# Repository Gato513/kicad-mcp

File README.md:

# kicad-mcp

An MCP (Model Context Protocol) server that lets an LLM agent operate
[KiCad](https://www.kicad.org/) directly — read schematics and PCBs in a
token-efficient format, place footprints, draw copper, run an autorouter,
validate with ERC/DRC, and export manufacturing files — through 32
purpose-built tools instead of raw file editing.

**Status:** past MVP. The full PCB write loop (placement → outline →
zones/GND plane → autorouting → DRC → export) has been closed and
re-validated against real KiCad 10.0.4 for months. It is now in a
pre-release consolidation phase: a structured [Validation
Suite](validation-suite/) exercises the flow against real open-hardware
projects to find where it actually breaks, on purpose, before anyone else
does. See [Known limitations](#known-limitations) below — this README
leads with them rather than burying them.

## What it does

kicad-mcp automates the canonical KiCad PCB flow: place footprints → draw
board outline → add copper zones/GND plane → route with
[Freerouting](https://github.com/freerouting/freerouting) (headless
autorouter) → refill zones and re-run DRC → export gerbers/BOM/renders.
State is exposed to the LLM agent as [TOON](docs/specs/toon-v1.md), a
compact encoding designed to keep token usage low across many small tool
calls rather than re-serializing the whole board every time.

It talks to a **running KiCad instance** over KiCad's own local IPC API
(`kicad-python`) for live edits, and shells out to `kicad-cli` for
DRC/ERC/export — it does not parse or hand-edit `.kicad_pcb`/`.kicad_sch`
files itself for PCB work (schematic editing is the one exception, see
limitation 7 below).

**Validated scale, stated plainly:** the flow has completed end-to-end,
with results within the project's own acceptance thresholds, on boards up
to **63 footprints / 48 nets / 2 layers**. It was also run against a
**437-footprint / 380-net / 4-layer** board (HackRF One) specifically to
find the scaling ceiling — the autorouter did not complete on that board
(see limitation 2). Treat "small-to-medium 2-layer board" as the
demonstrated sweet spot today, not "any KiCad project."

## Quickstart

```bash
git clone https://github.com/Gato513/kicad-mcp.git
cd kicad-mcp
uv sync                                   # install dependencies (uv, https://docs.astral.sh/uv/)
python3 scripts/verificar_entorno.py      # environment check — run this before anything else
uv run pytest -m "not integration"        # offline unit + golden tests (394 passing today)
```

`verificar_entorno.py` tells you exactly what's missing for the mode
you're in (plain unit tests vs. tests that need a running KiCad) and
prints the fix, so start there rather than guessing at env vars.

To actually drive KiCad you need:
- KiCad ≥ 9.0 installed, 10.0.4 is the validated target (see
  [ADR-0002](docs/adr/0002-versiones-de-kicad.md)), with **Preferences →
  Plugins → Enable API server** turned on and KiCad restarted.
- `KICAD_MCP_PROJECT` set to the `.kicad_pro` you want the server to
  operate on.
- `KICAD_MCP_FREEROUTING_JAR` set to a local `freerouting-*.jar` if you
  want `route_board` to actually autoroute (Java ≥ 17 required — note
  Freerouting ≥ 2.2.3 itself needs Java 25; if your PATH `java` is
  older, point `KICAD_MCP_JAVA_EXE` at a compatible JDK instead of
  changing your system default).
- `KICAD_API_SOCKET` only if your KiCad API socket isn't at the default
  `ipc:///tmp/kicad/api.sock`.

Then register the server with an MCP client (`uv run kicad-mcp` runs it
over stdio) or probe it by hand with the official inspector:

```bash
npx @modelcontextprotocol/inspector uv run kicad-mcp
```

A minimal first call once connected: `health()` to confirm the bridge can
see your KiCad instance, then `run_drc()` against a project you don't
mind DRC-checking.

## Known limitations

This section exists because a colleague who tries this on their own board
deserves to know where it stops working *before* they hit it, not after.
Each item links to the session or document where it was found and
verified — nothing here is a guess.

- **Validated up to 63 footprints / 2 layers; a 437-footprint / 4-layer
  board found the scaling ceiling, not a routed result.** See
  [`docs/analisis/validation-suite-sintesis-A-B-C.md`](docs/analisis/validation-suite-sintesis-A-B-C.md)
  for the full three-point comparison (13 fp → 63 fp → 437 fp).
- **Freerouting 2.1.0 can enter an internal crash-loop on large/complex
  boards** (observed on the 437-footprint board: repeated internal
  `NullPointerException`s, no routing progress for a full hour). This is
  an upstream Freerouting issue, not a kicad-mcp bug — `route_board`
  itself behaved correctly on the timeout (no corrupted state). See
  [`docs/BACKLOG.md`](docs/BACKLOG.md) (`F-V3-ROUTER-TIMEOUT-HARD`).
- **`add_zone(fill=true)` can crash KiCad after 3-4 consecutive calls on
  large boards.** Root cause is not conclusively identified — code
  analysis found no bridge-side cause, and the failure signature (zone
  fragmentation) looks like a pcbnew fill behavior at scale, but this
  wasn't confirmed by reproduction this cycle. Workaround: call
  `fill_zones()` once at the end instead of `fill=true` per zone. Full
  writeup: [`docs/analisis/auditoria-contratos-bridge.md`](docs/analisis/auditoria-contratos-bridge.md) §4.
- **Most write tools don't save to disk by themselves.** Tools like
  `add_track`, `add_via`, `move_footprint` mutate the live, in-memory
  board and expect the caller to invoke `save_board()` explicitly. The
  tools that guarantee disk == memory when they return successfully are
  `route_board`, `fill_zones`, `add_zone(fill=true)`, and
  `delete_tracks_bulk` when the board has copper zones — see
  [ADR-0012](docs/adr/0012-route-board-persist-contract.md).
- **`delete_tracks_bulk` behaves differently depending on the board.** If
  the board contains at least one copper zone — a board-wide check, not a
  geometric test of whether the deletion actually touched that zone — it
  refills zones, re-enforces hole clearance and saves to disk before
  returning, raising `POST_ZONE_PERSIST_FAILED` if that save fails rather
  than succeeding silently. On a board with no copper zone it stays
  in-memory like the tools above, and `save_board()` is the caller's job.
  `delete_zone` and `add_keepout_zone` don't recompute neighboring zone
  fills on their own — tracked as `A2`/`A3` in
  [`docs/analisis/auditoria-contratos-bridge.md`](docs/analisis/auditoria-contratos-bridge.md) §5.2.
- **Freerouting doesn't treat a GND copper plane as an exclusion zone for
  nets it doesn't own** — it only routes to the plane's own net, not
  around it. A specific same-layer variant of the resulting orphaned-via
  pattern isn't fixed by the existing post-route stitching yet. See
  `F-D5-01-B` in [`docs/BACKLOG.md`](docs/BACKLOG.md).
- **Schematic editing is direct file mutation (`kicad-skip`), not IPC** —
  KiCad 10 doesn't expose a schematic API. This also means the schematic
  write tools (`add_symbol`, `set_value`, `set_footprint`,
  `connect_pins`) are purely additive today: there's no `delete_wire` or
  similar, so an agent can build a schematic but not clean one up. See
  [`docs/guias/guia-paleta.md`](docs/guias/guia-paleta.md) for the one
  real hazard this creates (never edit a schematic file while KiCad's
  own editor has it open).
- **Long-running tool calls (e.g. a full autoroute) can exceed an MCP
  client's idle timeout** (~1818s observed) before KiCad/Freerouting
  finishes. This is a client-side limitation, not a kicad-mcp bug —
  driving the call from a detached process (`nohup` + `disown`) works
  around it. See `docs/historico/sesiones/33-reporte.md`.
- **GUI-dependent tests require a human with KiCad open and are not
  automated** — this is a constraint of KiCad's IPC API on this version,
  not a project shortcut. See
  [`docs/guias/pruebas-gui.md`](docs/guias/pruebas-gui.md) for the manual
  protocol.
- **Practically Linux-only** ([ADR-0005](docs/adr/0005-linux-como-plataforma.md)).
  KiCad 10.0.4 is the validated target; 9.0 is the documented minimum
  ([ADR-0002](docs/adr/0002-versiones-de-kicad.md)).

## Documentation

- [`docs/analisis/validation-suite-sintesis-A-B-C.md`](docs/analisis/validation-suite-sintesis-A-B-C.md) — the
  cross-board evidence behind the scale claims above.
- [`docs/analisis/auditoria-contratos-bridge.md`](docs/analisis/auditoria-contratos-bridge.md) — full audit of
  every write tool's persistence/error/sync/reload contract.
- [`docs/adr/`](docs/adr/) — one architectural decision record per file
  (why KiCad 10, why stdio-only, why no database, the `route_board`
  persistence contract, etc.).
- [`docs/architecture-for-contributors.md`](docs/architecture-for-contributors.md)
  — start here if you're new: real process topology, tool taxonomy, and
  how to navigate the ADRs/specs/session-report layers below.
- [`docs/DECISIONES.md`](docs/DECISIONES.md) — index of ADRs plus
  informal decisions not yet promoted to one.
- [`docs/investigacion/`](docs/investigacion/) — root-cause
  investigation reports for specific bugs.
- [`docs/glosario.md`](docs/glosario.md) — EDA/KiCad domain glossary.
- [`docs/guias/guia-paleta.md`](docs/guias/guia-paleta.md) — protocol for
  populating a schematic with `add_symbol`.
- [`docs/guias/pruebas-gui.md`](docs/guias/pruebas-gui.md) — manual test
  protocol for the GUI-dependent test suite.
- [`docs/INDEX.md`](docs/INDEX.md) — full documentation map, if you need
  something not linked above.

## Contributing

Contributions are welcome. [`CONTRIBUTING.md`](CONTRIBUTING.md) covers
setup, the project's write-tool contract (the 4 axes every write tool is
checked against), and the review conventions that shaped the codebase —
read it before opening a PR that touches anything under `src/kicad_mcp/tools/`
or `src/kicad_mcp/bridge/`.

## License

Apache License 2.0 — see [`LICENSE`](LICENSE). Runtime dependencies with
other licenses (KiCad and Freerouting are GPL-3.0, invoked as external
processes rather than linked; `kicad-skip` is LGPL-2.1) are listed in
[`NOTICE`](NOTICE).

## Acknowledgments

- [KiCad](https://www.kicad.org/) — the EDA platform this project
  automates, not replaces.
- [Freerouting](https://github.com/freerouting/freerouting) — the
  headless autorouter `route_board` drives. Its 2.1.0 crash-loop on large
  boards is a real, documented limitation (see above) — it's still the
  best open autorouter available for this integration.
- [ANAVI Technology](https://anavi.technology/) and [Great Scott
  Gadgets](https://greatscottgadgets.com/) — authors of the real
  open-hardware designs (`anavi-dev-mic`, `anavi-macro-pad-12`,
  `hackrf-one`) used as ground truth in the Validation Suite.
- Built with heavy use of Claude (Anthropic) as the agentic development
  environment throughout this project's write-tool implementation and
  validation cycles — noted here for transparency about how the codebase
  was produced, not as an endorsement of any particular workflow.

*(También disponible en [español](README.es.md).)*

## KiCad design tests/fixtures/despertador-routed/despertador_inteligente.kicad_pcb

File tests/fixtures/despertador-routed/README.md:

# Fixture `despertador-routed`

## Actualizado en sesión 29 (Dogfooding 7, 2026-07-25, commit base `6479923`)

Este fixture fue **regenerado desde cero** en la sesión 29 (Dogfooding 7,
tercer dogfooding de Fase 3), partiendo del mismo esquemático corregido de
sesión 19b usado en D3-D6 (0 errores ERC, 4 warnings `lib_symbol_mismatch`
aceptados — D-19b.1). Reemplaza al fixture de sesión 28 (D6): misma placa,
misma topología eléctrica, **colocación física nueva** (V6 de D7 — 23
coordenadas propias, distintas de D5/D6, decididas por el agente en clusters
funcionales dispuestos en anti-diagonal, no imitación de D5/D6).

**Objetivo de D7:** (a) 3er verde consecutivo del criterio de cierre de
Fase 3 (D5=9.5, D6=9.7, D7=9.8 — ver detalle abajo); (b) aislar
correctamente el efecto de D-26.1 (sesión 26) replicando el orden de fases
exacto de D5 (plano GND creado ANTES de la colocación, D-28.1 vinculante) —
a diferencia de D6, donde el orden invertido dejó el experimento
confundido; (c) variación geométrica controlada (V6) para que la evidencia
de D-23.2/D-26.1 no dependa de un único layout; (d) protocolo F-D6-01 (V7):
3 mediciones adicionales de re-ruteo parcial para cerrar la vigilancia
sobre el costo de `route_board` en re-ruteos parciales. Ver
`/tmp/dogfood7-fricciones.md` (log completo de la sesión, no versionado)
para el detalle de las 4 corridas completas de ruteo + experimento V4.

- Topología de red: idéntica a D3-D6 (`/NSS` separado de `/MOSI`, `/SCL`
  limpio, No-Connect explícitos en U2.INT/U3.~INT/U3.VLED+).

## Uso

Estos tests son `integration_gui`: necesitan KiCad vivo con **una copia**
de este fixture abierta (no hay `open_project` programático en kipy/KiCad
10). Ver `docs/pruebas-gui.md §fixture despertador-routed` para el
protocolo completo. **Ningún test de este repo hardcodea las coordenadas de
colocación** — todos derivan bbox/zonas/posiciones en runtime (D-24.1), así
que el cambio de layout D6→D7 no afecta ninguna aserción existente.

## Estado del ruteo

- Board: 44×44mm (contorno `(125,60)`→`(169,104)`, idéntico a D3-D6), plano
  GND en B.Cu filled desde cero **antes** de la colocación (orden D5/D-28.1,
  no D6) y antes del ruteo (C2, Freerouting no respeta el plano como
  exclusión de nets ajenos — D-19.1 v6 — se resuelve con refill +
  `enforce_hole_clearance` + persistencia D-23.2 post-route).
- **Colocación (V6, coordenadas nuevas):** clusters funcionales en
  anti-diagonal — BT1 (batería) en la banda superior, cluster de potencia
  (C1/D1/TP1/TP2) arriba-derecha, J1+U1 (MCU, hub SPI/I2C) en banda media,
  U4 (RF) + ANT1 pegada a 2mm de distancia (vs 28mm en D5/D6) en el
  cuadrante inferior-derecho, cluster I2C (U2/U3/C5/C6/R1/R2/J2) en el
  cuadrante izquierdo. `get_footprint_neighbors` inclusivo (D-D4.1) corrido
  sobre BT1, U4, J1, J2, ANT1 antes de mover — con el outline ya creado
  (orden D-28.1), a diferencia de D6. Verificación read-only adicional de
  solapes de courtyard tras la colocación: 0 solapes, los 23 dentro del
  outline, ANT1 a 15mm del borde y J1 a 7.5mm (ambos muy por encima del
  mínimo 1.5-2mm de D-D3.1).
- **Experimento aislado D-26.1 (V4.a → V4.b, el punto metodológico central
  de D7):** con el orden de fases correcto (plano antes de colocar, sin
  confundir con D6), el baseline **sin** `fill_zones()` explícito (V4.a)
  reprodujo el patrón exacto de D5: **6 violaciones no-triviales** (3×
  `hole_clearance` J1 NPTH + 1× `hole_clearance` ANT1 + 1× `clearance`
  ANT1 + 1× `solder_mask_bridge` ANT1) — fill rancio del plano creado antes
  de mover los 23 footprints encima. El baseline **con** `fill_zones()`
  explícito (V4.b) llevó esas 6 violaciones a **0**. **Ratificación
  empírica de D-26.1 sin el confusor de orden de fases que tuvo D6** — el
  delta V4.a→V4.b es evidencia directa: el refill explícito es necesario
  en el flujo plano-antes-de-colocar, no redundante.
- Ruteo en **4 corridas completas de `route_board`** (1 desde cero + 3
  re-ruteos parciales del protocolo F-D6-01, sobre `+3V3` [alto grado de
  interconexión, 65 tracks], `/SDA` [medio, 29 tracks] y `/NSS` [bajo, 7
  tracks — mismo net medido en D5 y D6], cada uno con su corrida de
  `delete_tracks_bulk(dry_run=true)` previa — C3): 10/10 nets ruteables
  ruteadas en las 4 corridas, 0 bloqueadas. Corrida 1 (desde cero):
  **40.6s**. Re-ruteos parciales: **23.7s / 24.4s / 17.7s** — ni tan
  baratos como los de D5 (~9-10s) ni tan caros como los de D6 (110-112s);
  sin correlación observable con el grado de interconexión del net dentro
  de esta sesión. Con N=7 total (2 D5 + 2 D6 + 3 D7) el rango 9s-112s no
  muestra patrón correlacional claro con interconexión/tamaño/capas — **se
  cierra F-D6-01 como variabilidad inherente de Freerouting/JVM**, sin
  activar el trigger de promoción a P2 (que requería >60s consistente).
- **DRC final: 0 errores, 0 warnings en las 4 corridas de ruteo.** Ninguna
  corrida introdujo un error nuevo (delta V4 = 0 en las 4, contra el
  baseline canónico V4.b).
- **F-D5-01 (isla GND sin vía al plano) NO reapareció** — corrida 1 y las 3
  parciales terminaron todas con `err_post=0` total, sin ningún
  `unconnected_items` residual. D5=sí (1 ocurrencia), D6=no, D7=no — el
  trigger de promoción a P2 ("2/3 dogfoodings") **no se cumple** (1/3).
- Gerbers (G3) y BOM exportados sin error, gate G3 pasó limpio.

## Ratificación de D-23.2 extendido (ADR-0012, sesión 27) en dogfooding real

**D7 (sesión 29) verificó 3/3 (o más) corridas coincidentes por cada una de
las tres tools cubiertas por el contrato:**

| Tool | Corridas V2 | Coincidencias | Divergencias |
|---|---|---|---|
| `route_board` | 4 (1 completa + 3 re-ruteos parciales, protocolo V7) | 4/4 | 0 |
| `fill_zones` | 3 (D-26.1 explícito V4.b + 2 zonas de test F.Cu) | 3/3 | 0 |
| `add_zone(fill=true)` | 3 (plano GND real + 2 zonas de test F.Cu) | 3/3 | 0 |

En las 10 corridas totales: `run_drc()` independiente inmediato coincidió
exacto con el estado reportado/persistido, mtime del `.kicad_pcb` cambió en
las 10, cero `EXTERNAL_EDIT_DETECTED` espurio. Combinado con las 9/9 de D6 y
las 5/5 previas de `route_board` (sesiones 24/25) y el 2/2 del test aislado
de sesión 27 para `fill_zones`/`add_zone`, el contrato D-23.2 extendido
queda ratificado en las tres tools desde cuatro ángulos distintos de
evidencia (unit/regresión, D5, D6, D7) sin ninguna divergencia registrada —
**3er verde consecutivo de Fase 3, criterio de convergencia cumplido.**

## ⚠️ Advertencia — no es referencia de diseño de colocación óptima

El esquemático y la topología eléctrica son correctos y representan el
diseño real del despertador. La **colocación física** fue diseñada por el
agente en D7 (sesión 29, tiempo acotado, variación geométrica deliberada
respecto a D5/D6) — sirve para ejercitar cobre denso, zonas, vías y el
pipeline completo schematic→gerbers, pero no está optimizada para RF
(antena) ni para producción en serie sin revisión humana adicional. En
particular, ANT1 quedó mucho más cerca de U4 (2mm) que en D5/D6 (28mm) —
deliberado para variar la geometría, no una recomendación de diseño RF.

## Regenerar el fixture (si el esquemático vuelve a cambiar)

1. Copiar el proyecto fuente a un directorio de trabajo (`/tmp/...`),
   nunca mutar este fixture in-place.
2. Abrirlo en KiCad (PCB Editor) — dejarlo abierto y no volver a tocarlo
   desde la GUI durante los pasos siguientes.
3. Un solo proceso Python/sesión MCP persistente para todas las llamadas
   a `route_board` (ver advertencia histórica sobre `live_stale` más
   abajo).
4. Requiere `KICAD_MCP_FREEROUTING_JAR` apuntando al jar de Freerouting.
5. Si no tiene contorno Edge.Cuts todavía, llamar `draw_board_outline`
   PRIMERO, y crear/fillar el plano GND (`add_zone`) **antes de la
   colocación masiva de footprints** — D-28.1 vinculante, cualquier
   inversión de este orden requiere `AskUserQuestion` al arquitecto y
   contamina la medición de D-26.1 (ver hallazgo de D6). Freerouting
   respeta `(plane)` nativo (D-19.1).
6. Tras la colocación masiva (`move_footprint` × N) y antes de leer
   cualquier baseline DRC, correr `fill_zones()` **explícito** — D-26.1
   (sesión 26, ratificado sin confusor en D7): `move_footprint` no dispara
   refill de zonas, un baseline leído sin este paso mide fill rancio (D7
   lo confirmó: 6 violaciones fantasma sin el refill, 0 con él).
7. El refill interno de `route_board`/`fill_zones`/`add_zone(fill=true)`
   ya recalcula `hole_clearance` correctamente y persiste antes de
   reportar (D-23.2, ADR-0012, extendido sesión 27 a las tres tools,
   ratificado 3/3+ por tool en D6 y D7). **No hace falta** el workaround
   manual de `delete_zone`+`add_zone(fill=true)` que el fixture de sesión
   20 (D3) documentaba como obligatorio — obsoleto desde sesión 24,
   ratificado en D5, D6 y D7. Seguí corriendo `run_drc()` propio como
   cross-check de todos modos (buena práctica, no por desconfianza en el
   contrato).
8. Verificar el JSON de `route_board`: `drc.por_tipo` sin
   `copper_edge_clearance`, `nets.bloqueadas` idealmente vacío. Luego
   `run_drc()` manual para confirmar (coincide con `err_post` si D-23.2 se
   sostiene — ver sección de ratificación arriba).
9. Copiar `.kicad_pcb`/`.kicad_pro`/`.kicad_sch`/`.kicad_prl`
   inmediatamente del directorio de trabajo a
   `tests/fixtures/despertador-routed/` — antes de correr cualquier otra
   tool que pueda volver a disparar el save implícito.

### Nota histórica: constraint de `live_stale`

`route_board` hace un "save_board implícito" (live→disco) si el board
abierto coincide con el target y el store en memoria no está
`live_stale` — pero ese flag vive en memoria del PROCESO servidor, no
persiste entre invocaciones. Si se corre `route_board` desde scripts
nuevos repetidamente, cada uno arranca con `live_stale=False`, dispara el
save implícito, y pisa el ruteo en disco con el estado viejo de la GUI
antes de re-rutear desde cero (hallazgo de sesión 17). Con un cliente MCP
real de un agente (proceso persistente, como en sesiones 20, 25, 28 y 29)
esto no pasa.

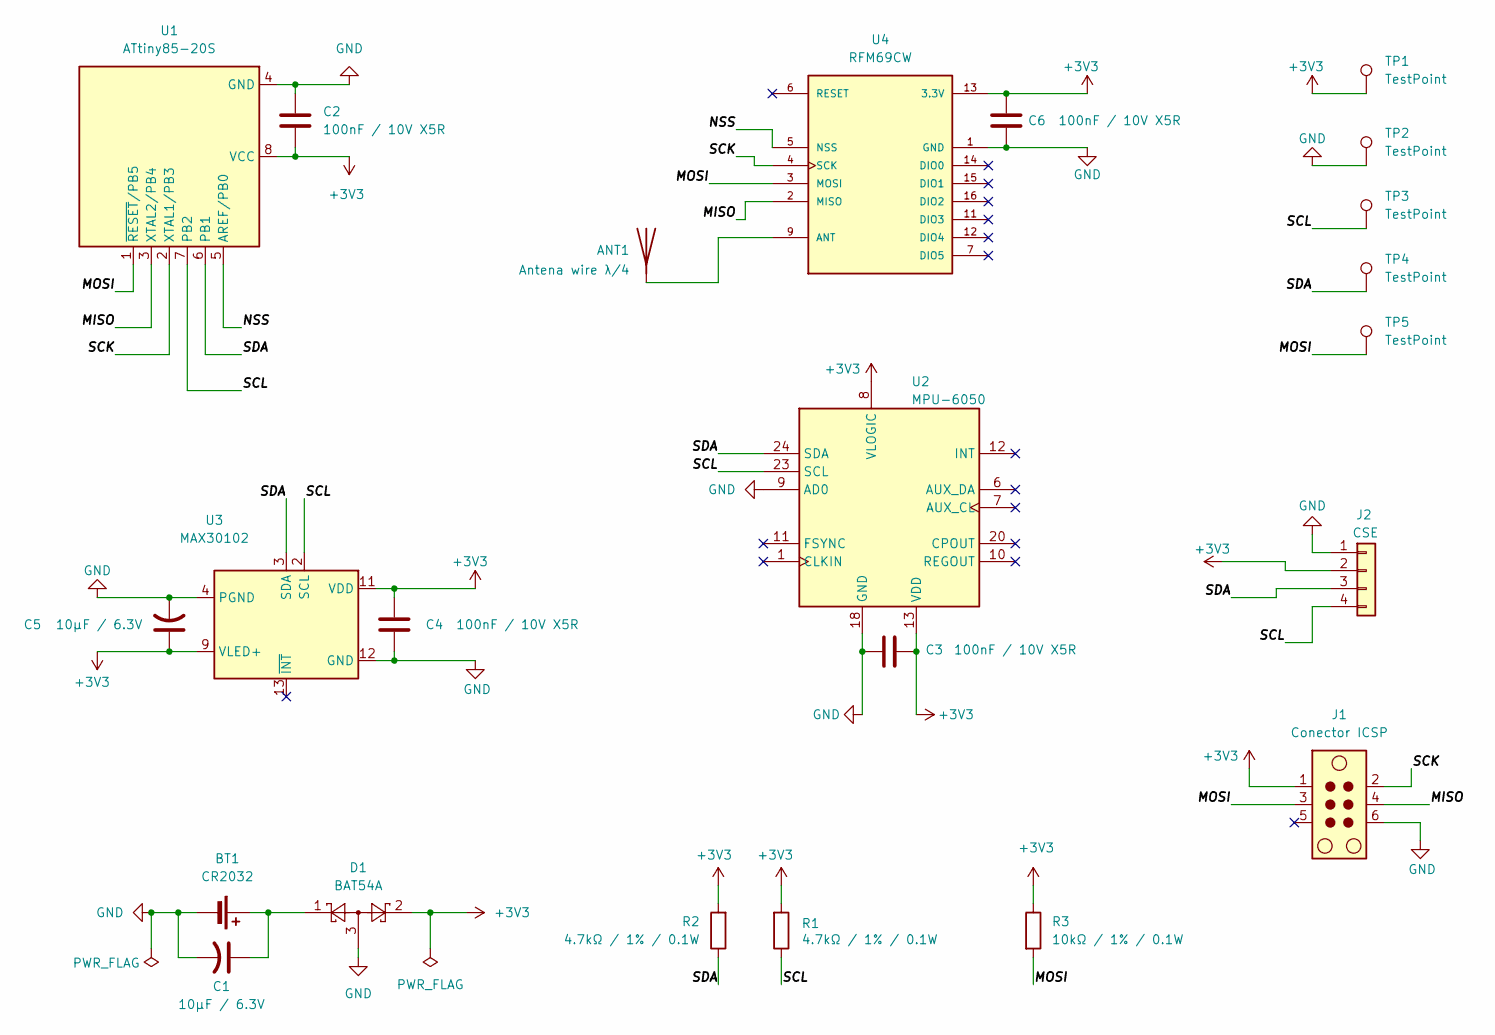
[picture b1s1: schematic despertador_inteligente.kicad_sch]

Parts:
ANT1: Antena wire λ/4; TestPoint_Plated_Hole_D2.0mm
BT1: CR2032; BatteryHolder_Keystone_3034_1x20mm
C1, C5: 10µF / 6.3V; C_0805_2012Metric
C2, C3, C4, C6: 100nF / 10V X5R; C_0402_1005Metric
D1: BAT54A; SOT-23
J1: Conector ICSP; Tag-Connect_TC2030-IDC-NL_2x03_P1.27mm_Vertical
J2: CSE; JST_SH_SM04B-SRSS-TB_1x04-1MP_P1.00mm_Horizontal
R1, R2: 4.7kΩ / 1% / 0.1W; R_0402_1005Metric
R3: 10kΩ / 1% / 0.1W; R_0402_1005Metric
TP1, TP2, TP3, TP4, TP5: TestPoint; TestPoint_Pad_D2.0mm
U1: ATtiny85-20S; SOIC-8_5.3x5.3mm_P1.27mm
U2: MPU-6050; InvenSense_QFN-24_4x4mm_P0.5mm
U3: MAX30102; Maxim_OLGA-14_3.3x5.6mm_P0.8mm
U4: RFM69CW; MOD_RFM69CW

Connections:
+3V3: C2.2, C3.2, C4.1, C5.1, C6.2, D1.2, J1.1, J2.2, R1.2, R2.2, R3.1, TP1.1 (1_1), U1.8 (VCC), U2.8 (VLOGIC), U2.13 (VDD), U3.9 (VLED+), U3.11 (VDD), U4.13 (3.3V)
/MISO: J1.4, U1.3 (XTAL2/PB4), U4.2 (MISO)
/MOSI: J1.3, R3.2, TP5.1 (1_1), U1.1 (~RESET/PB5), U4.3 (MOSI)
/NSS: U1.5 (AREF/PB0), U4.5 (NSS)
/SCK: J1.2, U1.2 (XTAL1/PB3), U4.4 (SCK)
/SCL: J2.4, R1.1, TP3.1 (1_1), U1.7 (PB2), U2.23 (SCL), U3.2 (SCL)
/SDA: J2.3, R2.1, TP4.1 (1_1), U1.6 (PB1), U2.24 (SDA), U3.3 (SDA)
GND: BT1.2 (-), C1.2, C2.1, C3.1, C4.2, C5.2, C6.1, D1.3, J1.6, J2.1, TP2.1 (1_1), U1.4 (GND), U2.9 (AD0), U2.18 (GND), U3.4 (PGND), U3.12 (GND), U4.1 (GND)
unnamed: ANT1.1 (A_1), U4.9 (ANT)
unnamed: BT1.1 (+), C1.1, D1.1

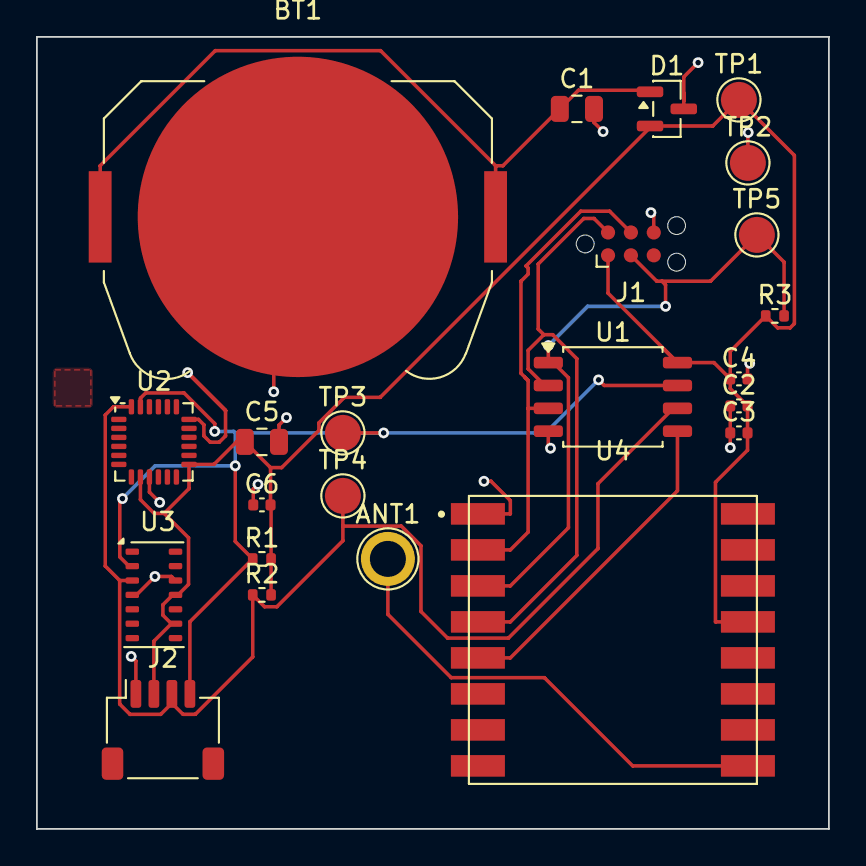
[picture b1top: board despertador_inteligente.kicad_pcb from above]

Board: 2 copper layers, 44.0 x 44.0 mm, 23 parts (0 on the bottom side), 10 nets.

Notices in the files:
parts and their libraries:
COPYRIGHT: Copyright 2012-2023 Great Scott Gadgets
LICENSE: Licensed under the CERN-OHL-P v2
